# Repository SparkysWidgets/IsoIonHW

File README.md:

Welcome To: IsoIon Hardware Repo!!
================================

##### Note: This is for the IsoIon Hardware Version 01 Branch

IsoIon Hardware Design Files in EAGLE. IsoIon is the first and only fully open source ISE interface with galvanic isolation. It only requires a single supply on the primary end, meaning no more pesky dual supply solutions with wallwarts or DC-DC converters everywhere. IsoIon is an Ion Selective Electrode Interface with 127 steps of programmable gain control which allows it to adapt to most ISE style probes. Great care was taken during part selection to create the best all around solution with great performance for the price. All components have been proven over the last several months(if not years) via other projects (MinipH, ISOBreakout, I2CADCBreakout, etc...). IsoIon is meant to be used in a wide array of installations from commercial products, Arduino and RaspPi Projects to lab usage. If you need to interface pH, Galvanic DO, ORP, Nitrate, or most other ISE style probes this is the interface for you!!!! Its meant to interface most platforms and even contains a Seeed Grove style connector for easy integration into the Grove environment.
Please respect the licensing on these designs, we all loose if licensing inst followed and proper credit is not given!

Schematic and General Info
-------------------------
##### The initial schematic is a bit messy sorry will clean up.

- Most of this design is proven from my other works, this is the culmination of lots of research and testing (others have copied my work beware of their closed designs)
- Single supply Isolation is provided by the pair of AD micromodules ADUM6010 iso DC-DC converter and the ADUM1251 I2C isolation module for hotswapping I2C systems on a I2C bus 
- Analog front end is boosted with an I2C digital pot in place of on leg of the gain control feedback loop (this is a proper reostat digipot IC). This gives us gain control so we can select what type of probe to interface pretty ingenious Special Thanks to Practical Maker for showing me a simpler way. I just automated his method and adjusted it to match how I interface probes (We both do it slightly different, difference is good in my opinion keep up your work PM!!!!)
- Negative voltage rail generation has been slightly improved I added in an output filter network that was tested to help a bit of the noise getting through to the amplification stage.
-I've updated the design to use a fixed 3.0v precision voltage reference ad the ADC VDD/VREF input, while the op-amp will still operate at 5v rails. I am pushing us up and out of the noise floor on both rails, you won't see this much elsewhere and probably wont until this proliferates. This design still meets my requirements for 2.7 to 5.5 VIN!
- Final amp stage to ADC has been properly filtered as per TI- app notes for matching ADCs to conditioning amps
- Reverse voltage protection using Afrotechmods Pfet method! Its all about VGS vs VDS hehe!

Board Layout Info
-------------------------
##### Form factor is the same width as the Mini line but was made a bit longer to accommodate the Isolation section from my ISOBreakout designs.

- Standard 2.54mm pitch header and Grove style connector is left in place
- Careful consideration on both part placement and trace layout is very important to overall success, we are dealing with 2 fully isolated ground planes.
- DC-DC converter topologies exist on this board, some will be in close proximity to the input stage. the Negative voltage rail generator is based on a charge pump at 250Khz we want to filter this out at the -5v output, but we want only enough bypass capacitance to filter these harmonics and a bit more general op-amp operation, since we have 1uF already at the chargepump. built RC network around .1uF as close to op-amp as possible, with 1uf supply at charge pump out put. Keep these traces short and surrounded by ground plane. 
- Proper placement and layout of the analog front end is crucial to achieve best performance characteristics. Guard rings must be used around the input leg of BNC, this is so often overlooked it makes me sad. Am I the only one who reads the app-notes datasheets and op-amp books??? If your probe is going to ground to your plane(ie non differential or instrumentation topo), make sure you control the current return path (this really isnt too much of a concern on pH interfacing but other probes can source mAs)
- As per above, Op-amp is mounted underside with minimal trace length to keep complex impedances/reactances to minimum, this lets us keep all the "hot" end of amplification stage inside a guard ring. As per op-amp operation the feedback loop output(into the - pin) will drive the guard ring to the same potential as the probe input pin so everything inside the ring will have enough drive to keep it there despite noise sources and outside influences, pretty cool huh! See layout of board to get a better idea, this is how an ideal guard ring should work (including both sides as shown with the small ring on top)
- The rest of the layout is just based on functional placements with minimal trace routing work, via count inst really an issue so burn them up if you want to make really nicely couple ground planes.
- Some test pad experimentation with the obvious ones marked in new "parts" GND, V+, V- with offset and pHVout test points near their usage points.
- REMEMBER ISOLATED GROUNDS DONT CROSS THEM, take measurements from each side with respect to its ground(reference) it is important to remember or else you may burn up the isolation ICs 
- Revers voltage protection added to both header VIN inputs, using a simple p-channel mosfet to since reverse voltages and switch off.

Errata
-------------------------

##### Just a quick list of current issues
- Mostly untested as a whole, but each part has been working for a while are are mature projects
- Silkscreen  as always could use some improvements.
- Care might be needed in measuring the digipots wiper to calculate the gain more accurately
- This thing is going to be awesome and change how we think of plain old pH interfaces!!!!!

Firmware
-------------------------

- Take a look in [isoIon's Firmware Repo](https://github.com/SparkysWidgets/IsoIonBFW) For Arduino!
- Check out my USB pH interface[LeoPhi](http://www.sparkyswidgets.com/Projects/LeoPhi.aspx) for a powerful and easy to use USB PH Probe interface!

Basic Usage
-------------------------

License Info
-------------------------

<p>This is a fully open source project released under the CC BY license</p>
<br />
<span xmlns:dct="http://purl.org/dc/terms/" property="dct:title">IsoIon</span> by <a xmlns:cc="http://creativecommons.org/ns#" href="www.sparkyswidgets.com" property="cc:attributionName" rel="cc:attributionURL">Ryan Edwards, Sparky's Widgets</a> is licensed under a <a rel="license" href="http://creativecommons.org/licenses/by-sa/3.0/deed.en_US">Creative Commons Attribution-ShareAlike 3.0 Unported License</a>.<br />
Based on a work at <a xmlns:dct="http://purl.org/dc/terms/" href="/portfolio-item/ion-selective-electrode-interface" rel="dct:source">https://www.sparkyswidgets.com/portfolio-item/ion-selective-electrode-interface</a>

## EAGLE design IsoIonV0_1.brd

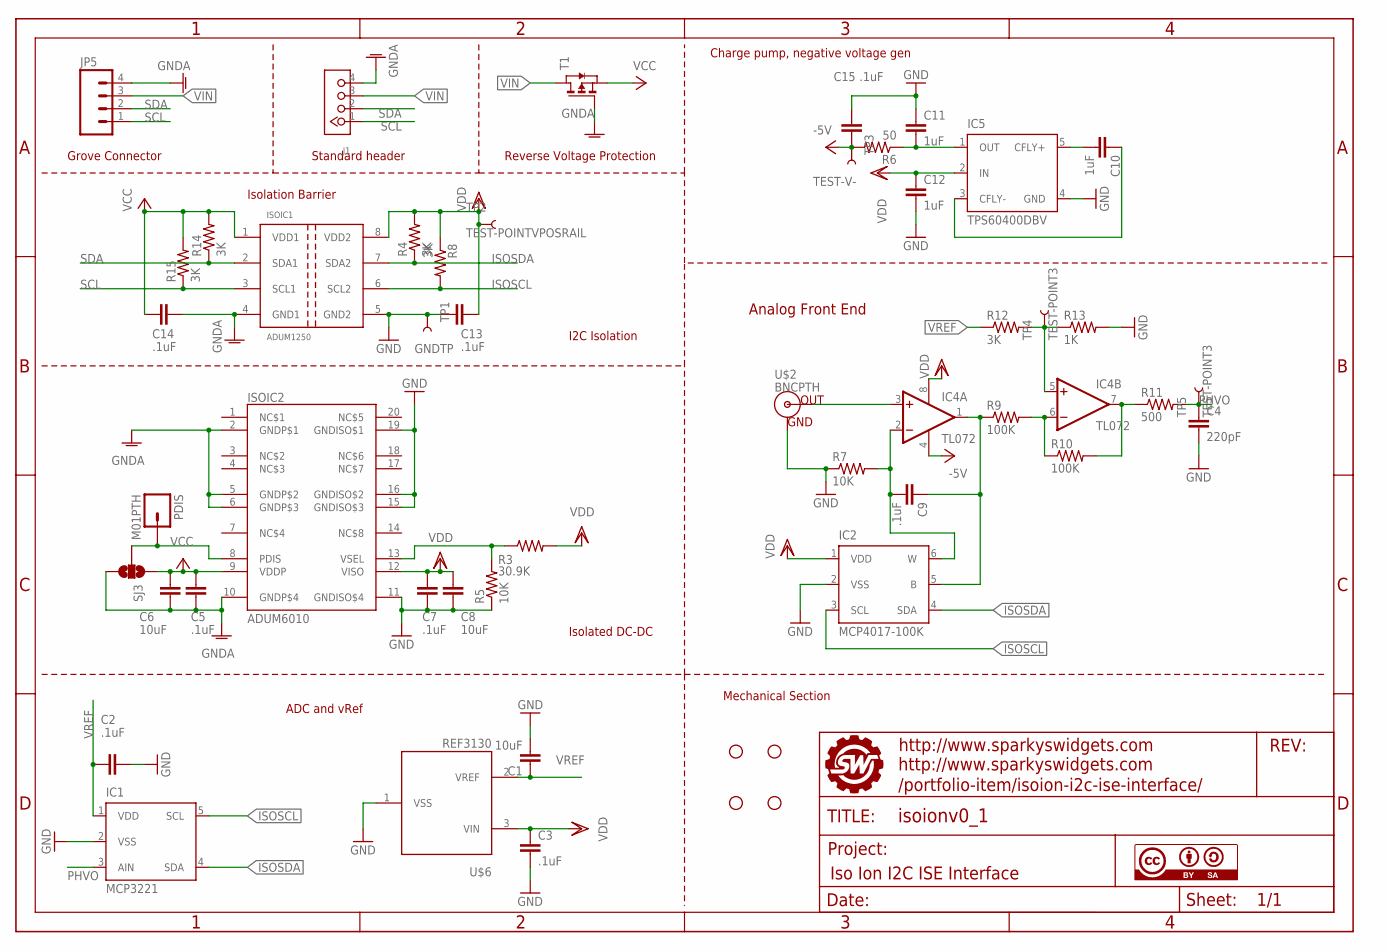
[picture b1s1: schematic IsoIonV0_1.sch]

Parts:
C1, C6, C8: 10uF; 0805
C2, C3, C5, C7, C9, C13, C14, C15: .1uF; 0805
C4: 220pF; 0805
C10, C11, C12: 1uF; 0805
IC1: MCP3221; SOT23-DBV
IC2: MCP4017-100K; SC70
IC4: TL072; SO08@1
IC5: TPS60400DBV; SOT23-DBV
ISOIC1: ADUM1250; SO08
ISOIC2: ADUM6010; SSOP20
J1: TWIG-4P-2.0-2.0; 4P-2.0
JP1, JP2, JP3, JP4: STAND-OFF
JP5: M04PTH; 1X04
PDIS: M01PTH; 1X01
R3: 30.9K; 0805
R4, R8, R12, R14, R15: 3K; 0805
R5, R7: 10K; 0805
R6: 50; 0805
R9, R10: 100K; 0805
R11: 500; 0805
R13: 1K; 0805
SJ3: SOLDERJUMPER_2WAYPASTE2&3; SJ_3_PASTE2&3
T1: PMOSSOT23; SOT-23
TP1: GNDTP; TEST_GND
TP2: TEST-POINTVPOSRAIL; TEST_V+
TP3: TEST-V-; TEST_V-
TP4, TP5: TEST-POINT3; PAD.03X.03
U$1: FRAME_ISOION; SWPCBLOGOWITHINFO
U$2: BNCPTH; BNC
U$3: CC-BY-SA
U$6: REF3130; SOT-23

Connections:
-5V: C15.2, IC4.4 (V-), R6.2, TP3.P$1
GND: C1.2, C2.1, C3.2, C4.2, C7.2, C8.2, C11.1, C12.2, C13.1, C15.1, IC1.2 (VSS), IC2.2 (VSS), IC5.4 (GND), ISOIC1.5 (GND2), ISOIC2.11 (GNDISO$4), ISOIC2.15 (GNDISO$3), ISOIC2.16 (GNDISO$2), ISOIC2.19 (GNDISO$1), R5.1, R7.1, R13.2, TP1.P$1, U$2.GND, U$6.1 (VSS)
GNDA: C5.2, C6.2, C14.1, ISOIC1.4 (GND1), ISOIC2.2 (GNDP$1), ISOIC2.5 (GNDP$2), ISOIC2.6 (GNDP$3), ISOIC2.10 (GNDP$4), J1.4, JP5.4, SJ3.3, T1.3 (G)
ISOSCL: IC1.5 (SCL), IC2.3 (SCL), ISOIC1.6 (SCL2), R8.2
ISOSDA: IC1.4 (SDA), IC2.4 (SDA), ISOIC1.7 (SDA2), R4.1
unnamed: IC4.5 (+IN), R12.2, R13.1, TP4.P$1
unnamed: IC4.7 (OUT), R10.2, R11.1
unnamed: IC4.6 (-IN), R9.2, R10.1
unnamed: ISOIC2.8 (PDIS), PDIS.1, SJ3.2
unnamed: ISOIC2.13 (VSEL), R3.1, R5.2
unnamed: C11.2, IC5.1 (OUT), R6.1
unnamed: IC4.3 (+IN), U$2.S (OUT)
unnamed: C9.2, IC2.6 (W), IC4.2 (-IN), R7.2
unnamed: C9.1, IC2.5 (B), IC4.1 (OUT), R9.1
unnamed: C10.1, IC5.3 (CFLY-)
unnamed: C10.2, IC5.5 (CFLY+)
PHVO: C4.1, IC1.3 (AIN), R11.2, TP5.P$1
SCL: ISOIC1.3 (SCL1), J1.1, JP5.1, R15.1
SDA: ISOIC1.2 (SDA1), J1.2, JP5.2, R14.1
VCC: C5.1, C6.1, C14.2, ISOIC1.1 (VDD1), ISOIC2.9 (VDDP), R14.2, R15.2, SJ3.1, T1.2 (S)
VDD: C3.1, C7.1, C8.1, C12.1, C13.2, IC2.1 (VDD), IC4.8 (V+), IC5.2 (IN), ISOIC1.8 (VDD2), ISOIC2.12 (VISO), R3.2, R4.2, R8.1, TP2.P$1, U$6.3 (VIN)
VIN: J1.3, JP5.3, T1.1 (D)
VREF: C1.1, C2.2, IC1.1 (VDD), R12.1, U$6.2 (VREF)

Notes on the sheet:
Grove Connector
Charge pump, negative voltage gen
Analog Front End
Isolation Barrier
Reverse Voltage Protection
Standard header
I2C Isolation
Isolated DC-DC
ADC and vRef
Mechanical Section

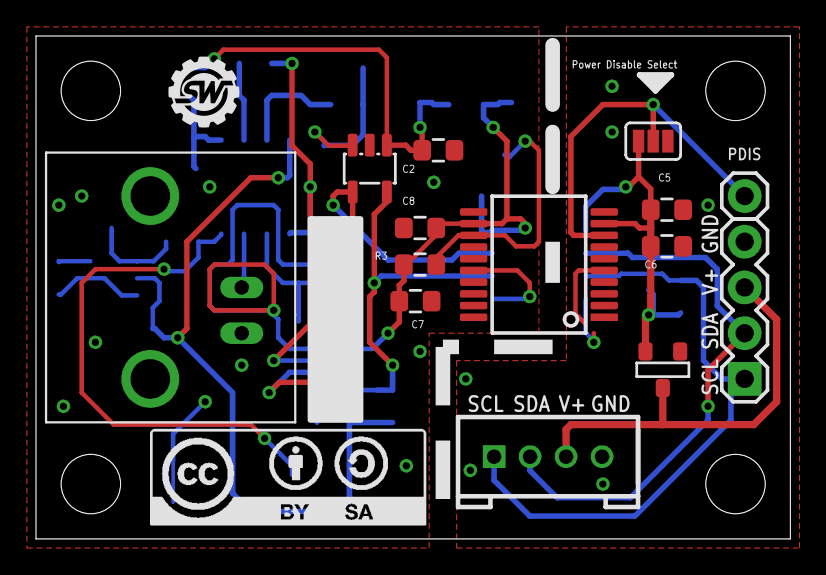
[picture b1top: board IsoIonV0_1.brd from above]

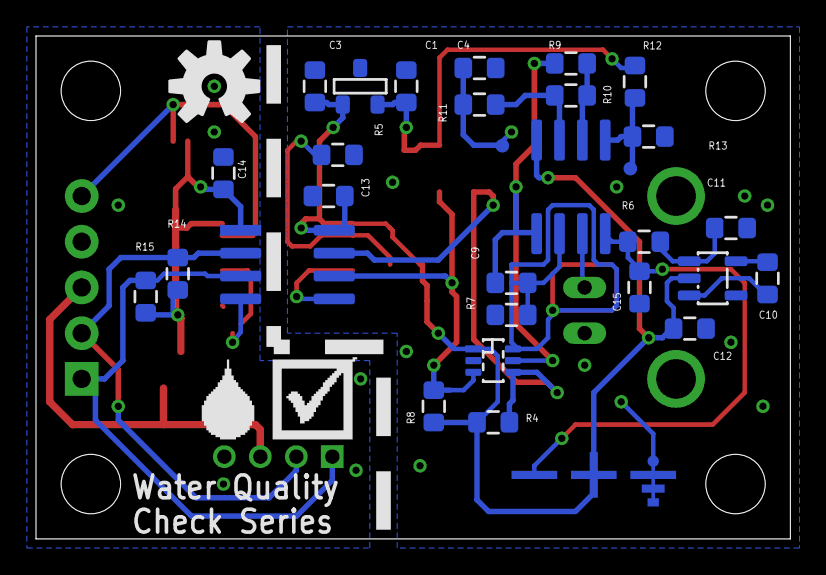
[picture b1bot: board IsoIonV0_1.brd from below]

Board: 2 copper layers, 41.9 x 27.9 mm, 56 parts (35 on the bottom side), 23 nets.

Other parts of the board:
U$4: OSHW-LOGO-M
U$7: SILK_ARROW
U$8: WATERCHECKLOGO2
U$9: WATERCHECKLOGO3

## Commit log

2014-04-20 Initial commit of IsoIon files, more to come oh yes much more to come!
2014-04-21 Standoff position fixed, was incorrectly offset
2014-04-21 a minor silkscreen adjustment
2014-04-22 Cleaned up sch small silkscreen adjustment on brd
2014-04-27 MCP4017 package updated to SC70-6
2014-05-02 Routed Offset from VREF instead of VDD
2014-05-02 Removed unsed VDD trace
2014-06-18 Flip pins on PMos reverse protection FET
